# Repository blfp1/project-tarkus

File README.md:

# Project Tarkus 🚀

## Overview
**Project Tarkus** is a custom development board designed for embedded systems study and prototyping, built around the **STM32G030K6T6** microcontroller.

The project started as a requirement for the **PBLE01** course at **UNIFEI**. The original specification required a 16x2 LCD and a temperature sensor. I decided to modernize the scope by replacing these with a **1.3" OLED Display** and a **Bluetooth LE module**, creating a more versatile platform for IoT projects.

## Key Features
* **Microcontroller:** STM32G030K6T6 (ARM Cortex-M0+, 32KB Flash, 8KB RAM).
* **Connectivity:**
    * **USB-C** for power and data.
    * **MCP2200** USB-to-UART Bridge for easy serial debugging.
    * **Bluetooth LE (HM-10)** interface for wireless communication.
* **User Interface:**
    * I2C header for **OLED Display** (SSD1306/SH1106).
    * **Rotary Encoder** with push-button for menu navigation.
    * 2x User LEDs.
* **Storage & RTC:** External I2C EEPROM (24LC512) and 32.768kHz Crystal for precise RTC.

## Design Decisions
One of the main challenges was the need for **two independent UART buses**: one for the Bluetooth module and another for the USB-Serial bridge. This requirement led to the selection of the **STM32G030K6**, which offers sufficient hardware UART peripherals, replacing the originally planned MCU.

## Repository Structure
* `Hardware/`: KiCad project files (Schematics, PCB Layout, Libraries).
* `Docs/`: Project documentation, schematics in PDF, and 3D renders.
* `Datasheets/`: Main components' technical documentation.

## Author
Designed by **Bernardo Lamim Fogaça de Padua**
*Institute of Systems Engineering and Information Technology - UNIFEI*

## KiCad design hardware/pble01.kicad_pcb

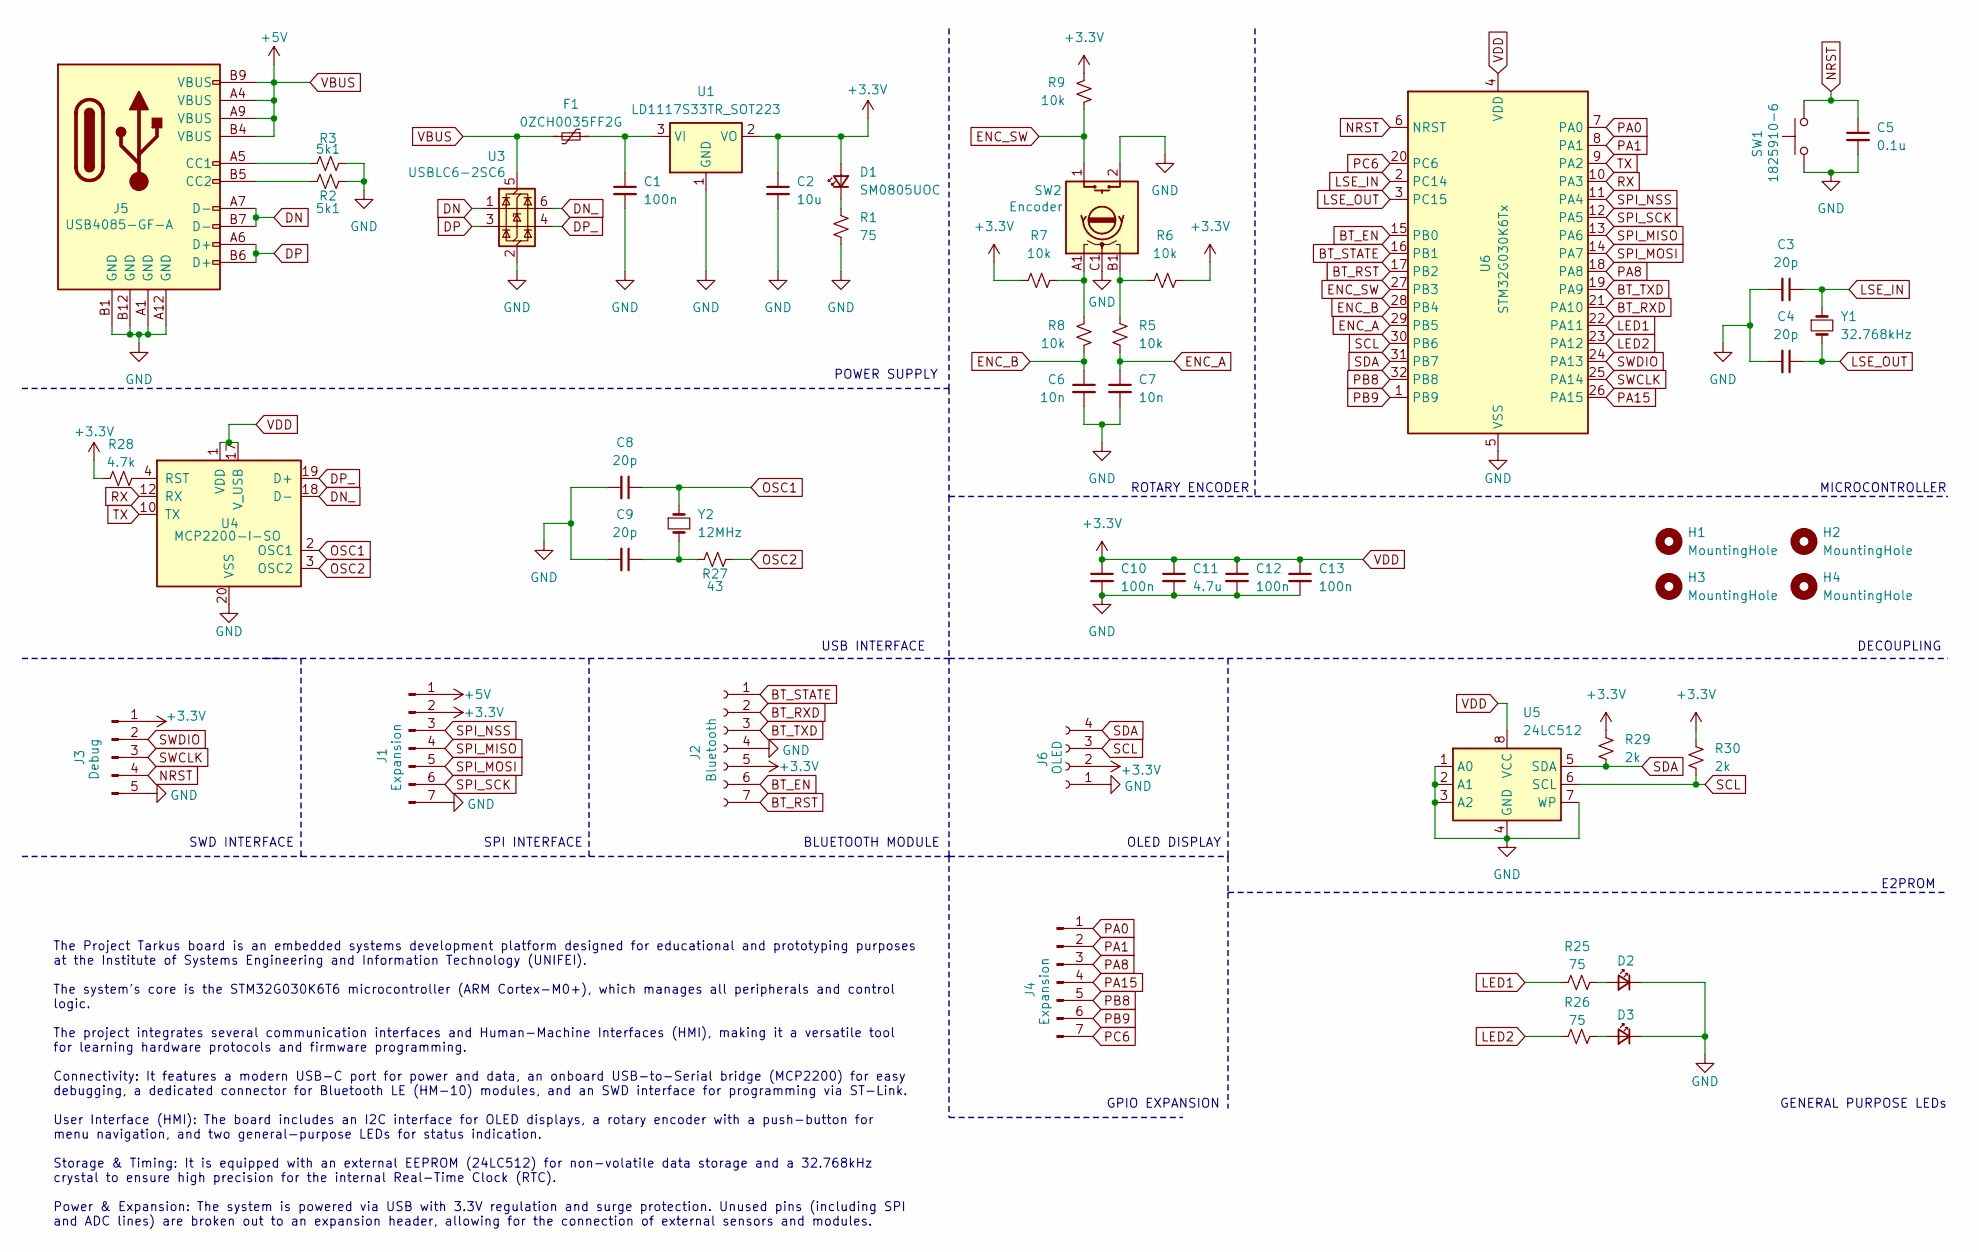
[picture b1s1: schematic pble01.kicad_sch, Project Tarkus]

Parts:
C1, C10, C12, C13: 100n; C_0805_2012Metric_Pad1.18x1.45mm_HandSolder
C2: 10u; C_0805_2012Metric_Pad1.18x1.45mm_HandSolder
C3, C4, C8, C9: 20p; C_0805_2012Metric_Pad1.18x1.45mm_HandSolder
C5: 0.1u; C_0805_2012Metric_Pad1.18x1.45mm_HandSolder
C6, C7: 10n; C_0805_2012Metric_Pad1.18x1.45mm_HandSolder
C11: 4.7u; C_0805_2012Metric_Pad1.18x1.45mm_HandSolder
D1, D2, D3: SM0805UOC; LED_0805_2012Metric_Pad1.15x1.40mm_HandSolder
F1: 0ZCH0035FF2G; Fuse_1210_3225Metric_Pad1.42x2.65mm_HandSolder
H1, H2, H3, H4: MountingHole; MountingHole_2.2mm_M2
J1, J4: Expansion; PinHeader_1x07_P2.54mm_Vertical
J2: Bluetooth; PinSocket_1x07_P2.54mm_Horizontal
J3: Debug; PinHeader_1x05_P2.54mm_Vertical
J5: USB4085-GF-A; USB_C_Receptacle_GCT_USB4085
J6: OLED; PinSocket_1x04_P2.54mm_Vertical
R1, R25, R26: 75; R_0805_2012Metric_Pad1.20x1.40mm_HandSolder
R2, R3: 5k1; R_0805_2012Metric_Pad1.20x1.40mm_HandSolder
R5, R6, R7, R8, R9: 10k; R_0805_2012Metric_Pad1.20x1.40mm_HandSolder
R27: 43; R_0805_2012Metric_Pad1.20x1.40mm_HandSolder
R28: 4.7k; R_0805_2012Metric_Pad1.20x1.40mm_HandSolder
R29, R30: 2k; R_0805_2012Metric_Pad1.20x1.40mm_HandSolder
SW1: 1825910-6; SW_PUSH_6mm_H7.3mm
SW2: Encoder; XDCR_PEC12R-4215F-S0024
U1: LD1117S33TR_SOT223; SOT-223-3_TabPin2
U3: USBLC6-2SC6; SOT-23-6
U4: MCP2200-I-SO; SOIC-20W_7.5x12.8mm_P1.27mm
U5: 24LC512; SOIC-8_3.9x4.9mm_P1.27mm
U6: STM32G030K6Tx; LQFP-32_7x7mm_P0.8mm
Y1: 32.768kHz; Crystal_DS26_D2.0mm_L6.0mm_Vertical
Y2: 12MHz; Crystal_HC49-4H_Vertical

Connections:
BT_EN: J2.6, U6.15 (PB0)
BT_RST: J2.7, U6.17 (PB2)
BT_RXD: J2.2, U6.21 (PA10)
BT_STATE: J2.1, U6.16 (PB1)
BT_TXD: J2.3, U6.19 (PA9)
DN: J5.A7 (D-), J5.B7 (D-), U3.1 (I/O1)
DN_: U3.6 (I/O1), U4.18 (D-)
DP: J5.A6 (D+), J5.B6 (D+), U3.3 (I/O2)
DP_: U3.4 (I/O2), U4.19 (D+)
ENC_A: C7.1, R5.1, U6.29 (PB5)
ENC_B: C6.1, R8.1, U6.28 (PB4)
ENC_SW: R9.1, SW2.1, U6.27 (PB3)
GND: C1.2, C2.2, C3.2, C4.2, C5.2, C6.2, C7.2, C8.2, C9.2, C10.2, C11.2, C12.2, C13.2, D2.1 (K), D3.1 (K), J1.7, J2.4, J3.5, J5.A1 (GND), J5.A12 (GND), J5.B1 (GND), J5.B12 (GND), J6.1, R1.2, R2.2, R3.2, SW1.1, SW2.2, SW2.C1, U1.1 (GND), U3.2 (GND), U4.20 (VSS), U5.1 (A0), U5.2 (A1), U5.3 (A2), U5.4 (GND), U5.7 (WP), U6.5 (VSS)
LED1: R25.1, U6.22 (PA11)
LED2: R26.1, U6.23 (PA12)
LSE_IN: C3.1, U6.2 (PC14), Y1.1
LSE_OUT: C4.1, U6.3 (PC15), Y1.2
NRST: C5.1, J3.4, SW1.2, U6.6 (NRST)
unnamed: C9.1, R27.1, Y2.2
unnamed: D1.1 (K), R1.1
unnamed: D2.2 (A), R25.2
unnamed: D3.2 (A), R26.2
unnamed: J5.A5 (CC1), R3.1
unnamed: J5.B5 (CC2), R2.1
unnamed: R5.2, R6.2, SW2.B1
unnamed: R7.1, R8.2, SW2.A1
unnamed: C1.1, F1.1, U1.3 (VI)
unnamed: R28.1, U4.4 (RST)
OSC1: C8.1, U4.2 (OSC1), Y2.1
OSC2: R27.2, U4.3 (OSC2)
PA0: J4.1, U6.7 (PA0)
PA1: J4.2, U6.8 (PA1)
PA8: J4.3, U6.18 (PA8)
PA15: J4.4, U6.26 (PA15)
PB8: J4.5, U6.32 (PB8)
PB9: J4.6, U6.1 (PB9)
PC6: J4.7, U6.20 (PC6)
RX: U4.12 (RX), U6.10 (PA3)
SCL: J6.3, R30.2, U5.6 (SCL), U6.30 (PB6)
SDA: J6.4, R29.2, U5.5 (SDA), U6.31 (PB7)
SPI_MISO: J1.4, U6.13 (PA6)
SPI_MOSI: J1.5, U6.14 (PA7)
SPI_NSS: J1.3, U6.11 (PA4)
SPI_SCK: J1.6, U6.12 (PA5)
SWCLK: J3.3, U6.25 (PA14)
SWDIO: J3.2, U6.24 (PA13)
TX: U4.10 (TX), U6.9 (PA2)
VBUS: F1.2, J1.1, J5.A4 (VBUS), J5.A9 (VBUS), J5.B4 (VBUS), J5.B9 (VBUS), U3.5 (VBUS)
VDD: C2.1, C10.1, C11.1, C12.1, C13.1, D1.2 (A), J1.2, J2.5, J3.1, J6.2, R6.1, R7.2, R9.2, R28.2, R29.1, R30.1, U1.2 (VO), U4.1 (VDD), U4.17 (V_USB), U5.8 (VCC), U6.4 (VDD)

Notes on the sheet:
POWER SUPPLY
OLED DISPLAY
SWD INTERFACE
USB INTERFACE
GENERAL PURPOSE LEDs
E2PROM
ROTARY ENCODER
The Project Tarkus board is an embedded systems development platform designed for educational and prototyping purposes at the Institute of Systems Engineering and Information Technology (UNIFEI). The system's core is the STM32G030K6T6 microcontroller (ARM Cortex-M0+), which manages all peripherals 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
SPI INTERFACE
DECOUPLING
GPIO EXPANSION
BLUETOOTH MODULE
MICROCONTROLLER

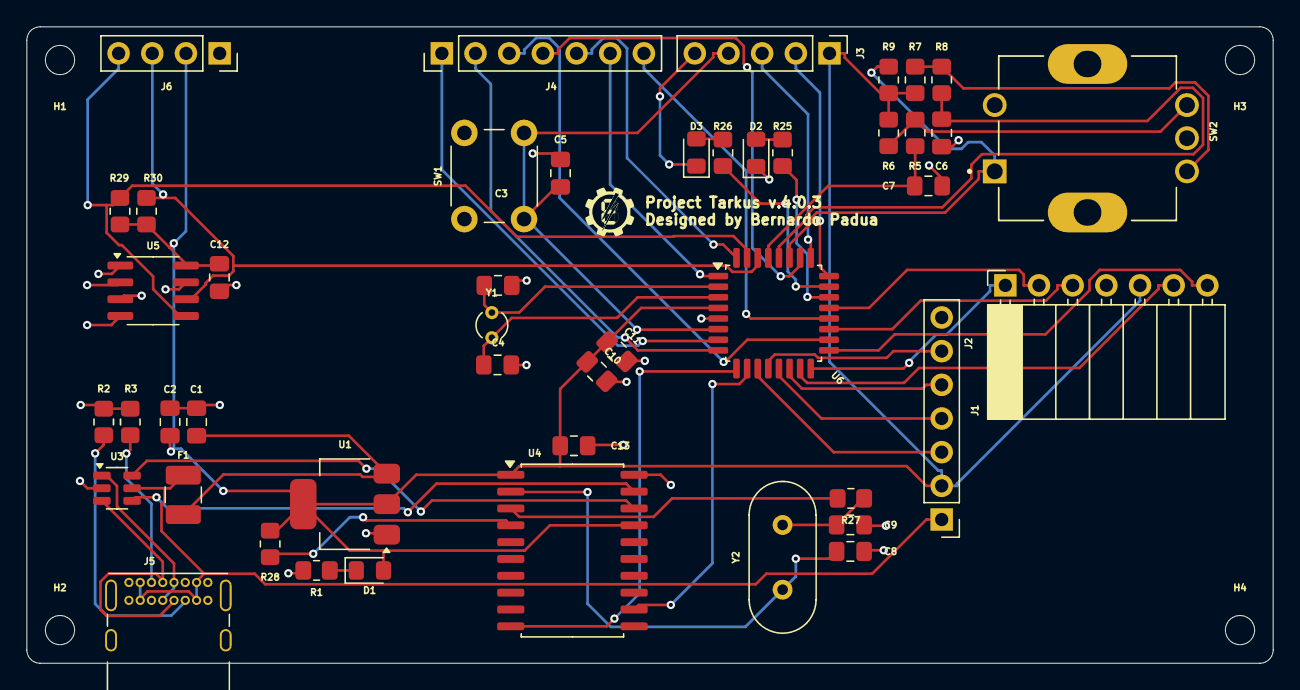
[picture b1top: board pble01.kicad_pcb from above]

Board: 2 copper layers, 94.0 x 48.0 mm, 50 parts (0 on the bottom side), 49 nets.

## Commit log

2025-12-23 Change project render image in README
    Updated the project render image and its note in README.
